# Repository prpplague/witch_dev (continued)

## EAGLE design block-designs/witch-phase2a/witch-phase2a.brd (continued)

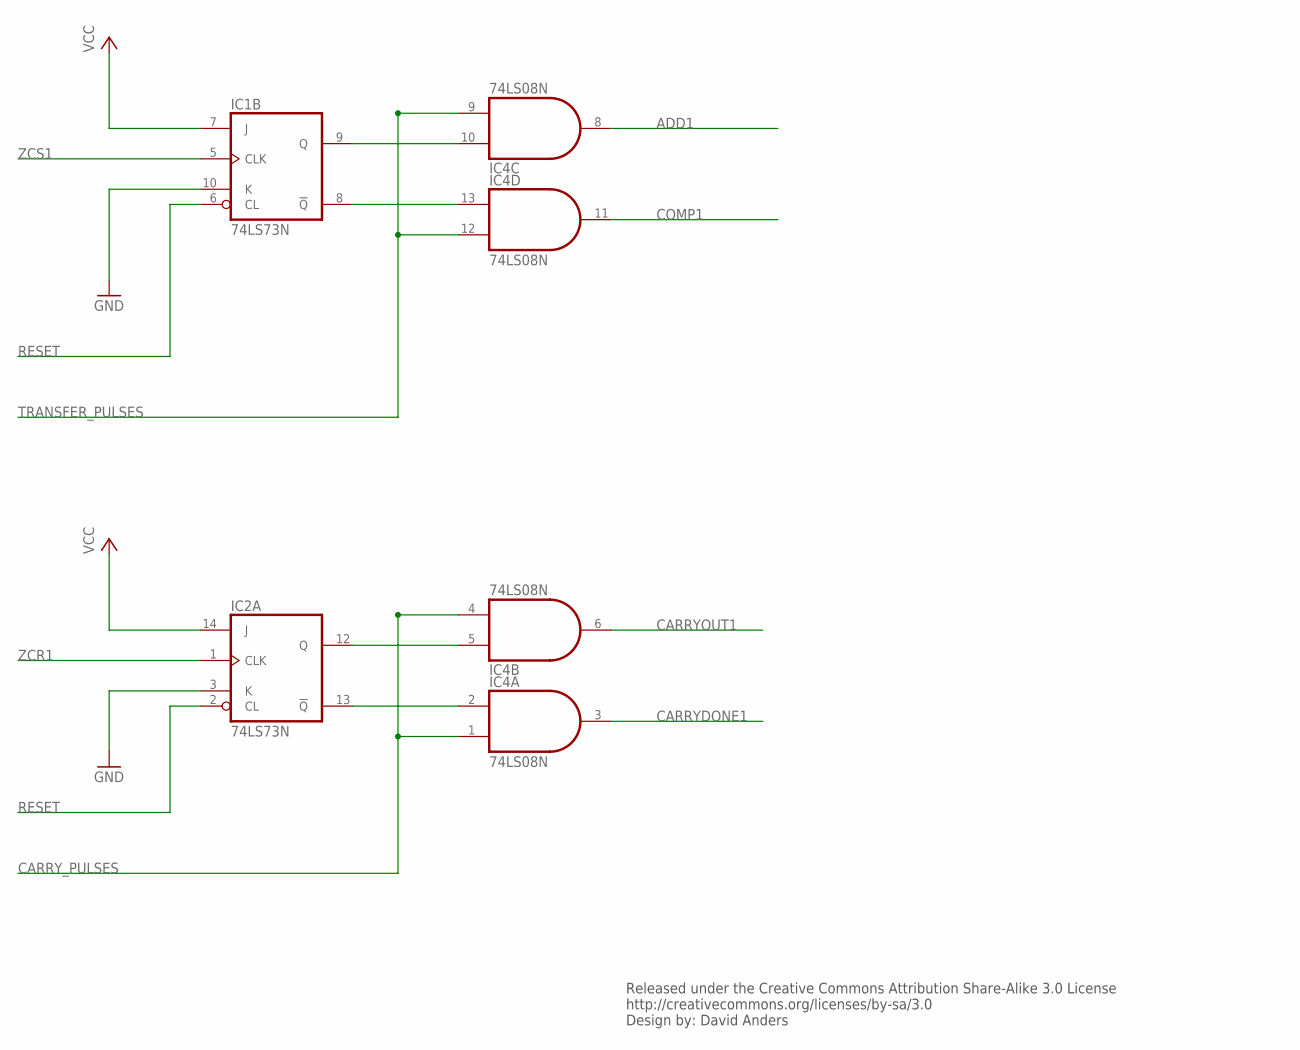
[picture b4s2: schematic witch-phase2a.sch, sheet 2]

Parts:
IC1, IC2: 74LS73N; DIL14
IC4: 74LS08N; DIL14

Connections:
ADD1: IC4.8 (O); also elsewhere on the board
CARRYDONE1: IC4.3 (O); also elsewhere on the board
CARRYOUT1: IC4.6 (O); also elsewhere on the board
CARRY_PULSES: IC4.1 (I0), IC4.4 (I0); also elsewhere on the board
COMP1: IC4.11 (O); also elsewhere on the board
GND: IC1.10 (K), IC2.3 (K); also elsewhere on the board
unnamed: IC2.12 (Q), IC4.5 (I1)
unnamed: IC2.13 (!Q), IC4.2 (I1)
unnamed: IC1.8 (!Q), IC4.13 (I1)
unnamed: IC1.9 (Q), IC4.10 (I1)
RESET: IC1.6 (CL), IC2.2 (CL); also elsewhere on the board
TRANSFER_PULSES: IC4.9 (I0), IC4.12 (I0); also elsewhere on the board
VCC: IC1.7 (J), IC2.14 (J); also elsewhere on the board
ZCR1: IC2.1 (CLK); also elsewhere on the board
ZCS1: IC1.5 (CLK); also elsewhere on the board

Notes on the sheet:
Released under the Creative Commons Attribution Share-Alike 3.0 License http://creativecommons.org/licenses/by-sa/3.0 Design by: David Anders

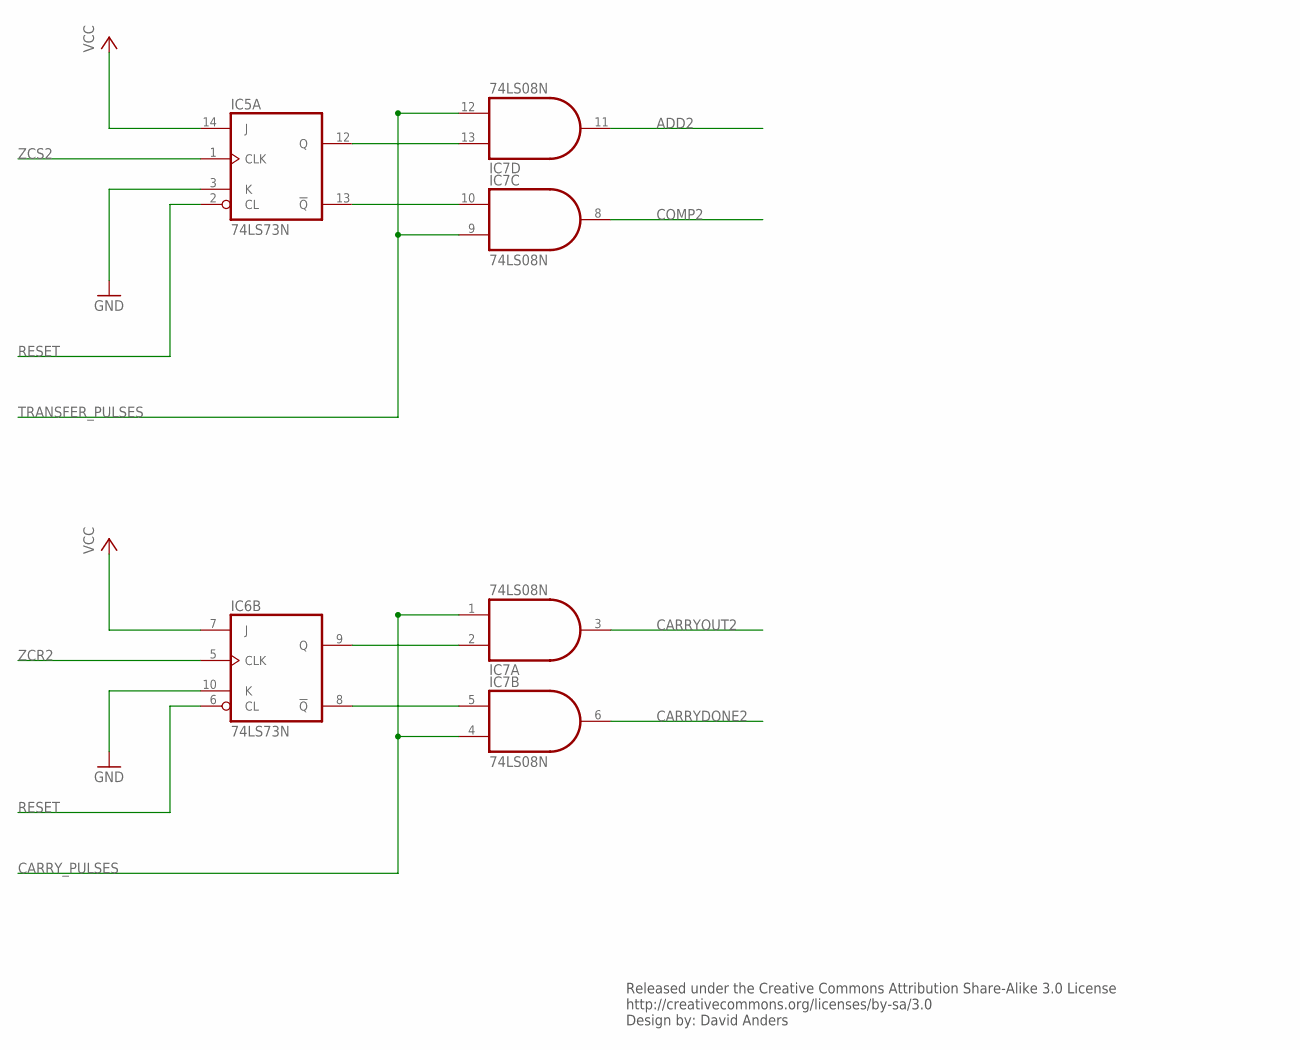
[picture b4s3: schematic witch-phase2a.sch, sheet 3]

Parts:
IC5, IC6: 74LS73N; DIL14
IC7: 74LS08N; DIL14

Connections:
ADD2: IC7.11 (O); also elsewhere on the board
CARRYDONE2: IC7.6 (O); also elsewhere on the board
CARRYOUT2: IC7.3 (O); also elsewhere on the board
CARRY_PULSES: IC7.1 (I0), IC7.4 (I0); also elsewhere on the board
COMP2: IC7.8 (O); also elsewhere on the board
GND: IC5.3 (K), IC6.10 (K); also elsewhere on the board
unnamed: IC6.8 (!Q), IC7.5 (I1)
unnamed: IC5.13 (!Q), IC7.10 (I1)
unnamed: IC5.12 (Q), IC7.13 (I1)
unnamed: IC6.9 (Q), IC7.2 (I1)
RESET: IC5.2 (CL), IC6.6 (CL); also elsewhere on the board
TRANSFER_PULSES: IC7.9 (I0), IC7.12 (I0); also elsewhere on the board
VCC: IC5.14 (J), IC6.7 (J); also elsewhere on the board
ZCR2: IC6.5 (CLK); also elsewhere on the board
ZCS2: IC5.1 (CLK); also elsewhere on the board

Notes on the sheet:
Released under the Creative Commons Attribution Share-Alike 3.0 License http://creativecommons.org/licenses/by-sa/3.0 Design by: David Anders

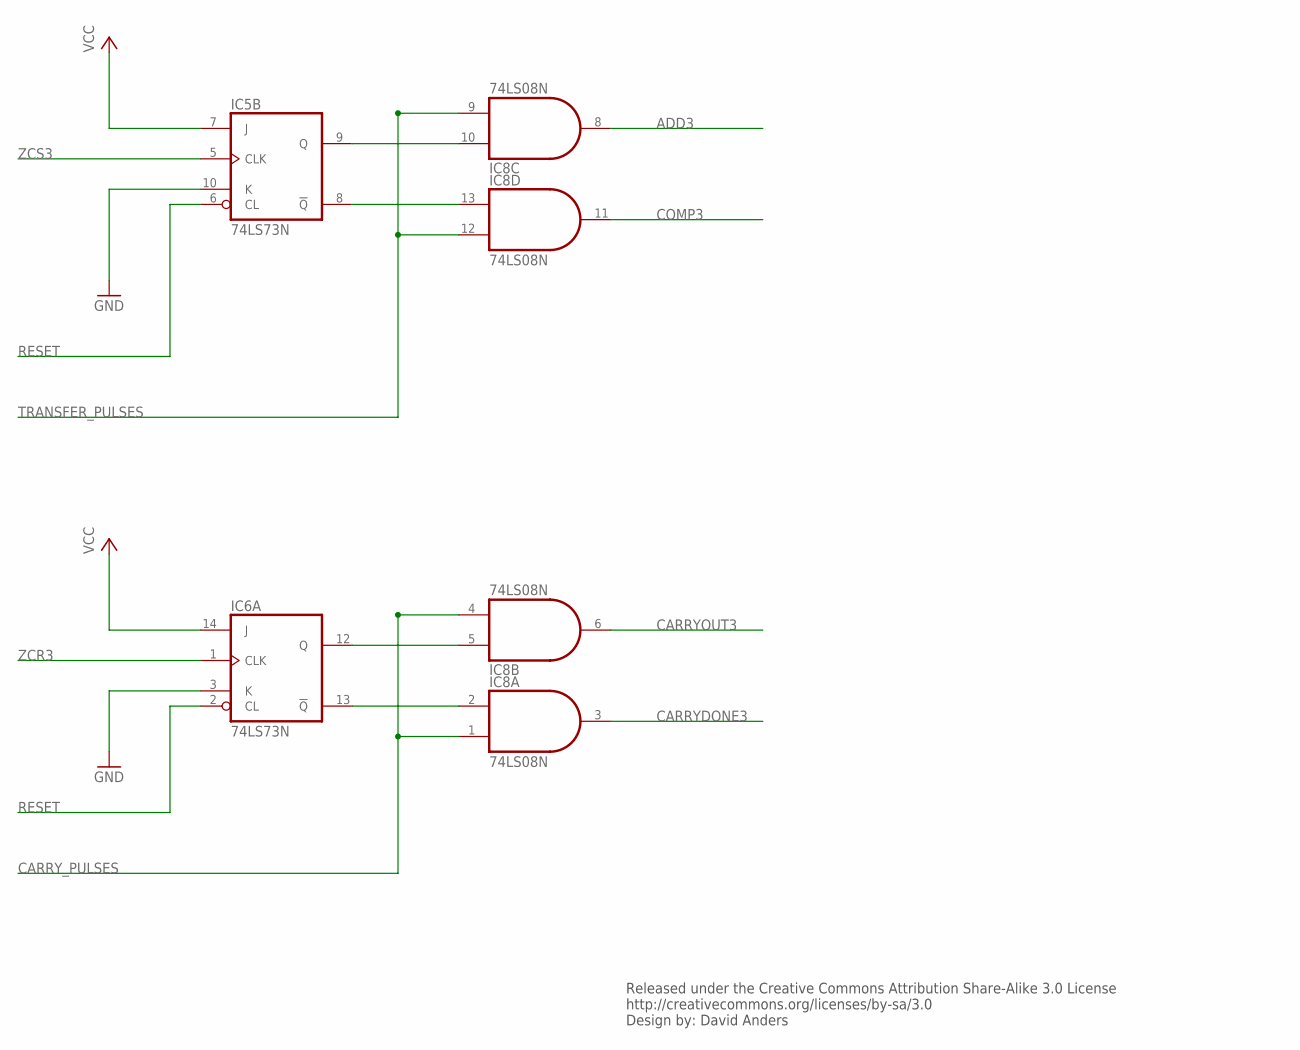
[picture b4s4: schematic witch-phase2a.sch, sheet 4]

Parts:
IC5, IC6: 74LS73N; DIL14
IC8: 74LS08N; DIL14

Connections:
ADD3: IC8.8 (O); also elsewhere on the board
CARRYDONE3: IC8.3 (O); also elsewhere on the board
CARRYOUT3: IC8.6 (O); also elsewhere on the board
CARRY_PULSES: IC8.1 (I0), IC8.4 (I0); also elsewhere on the board
COMP3: IC8.11 (O); also elsewhere on the board
GND: IC5.10 (K), IC6.3 (K); also elsewhere on the board
unnamed: IC6.13 (!Q), IC8.2 (I1)
unnamed: IC5.8 (!Q), IC8.13 (I1)
unnamed: IC5.9 (Q), IC8.10 (I1)
unnamed: IC6.12 (Q), IC8.5 (I1)
RESET: IC5.6 (CL), IC6.2 (CL); also elsewhere on the board
TRANSFER_PULSES: IC8.9 (I0), IC8.12 (I0); also elsewhere on the board
VCC: IC5.7 (J), IC6.14 (J); also elsewhere on the board
ZCR3: IC6.1 (CLK); also elsewhere on the board
ZCS3: IC5.5 (CLK); also elsewhere on the board

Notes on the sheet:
Released under the Creative Commons Attribution Share-Alike 3.0 License http://creativecommons.org/licenses/by-sa/3.0 Design by: David Anders

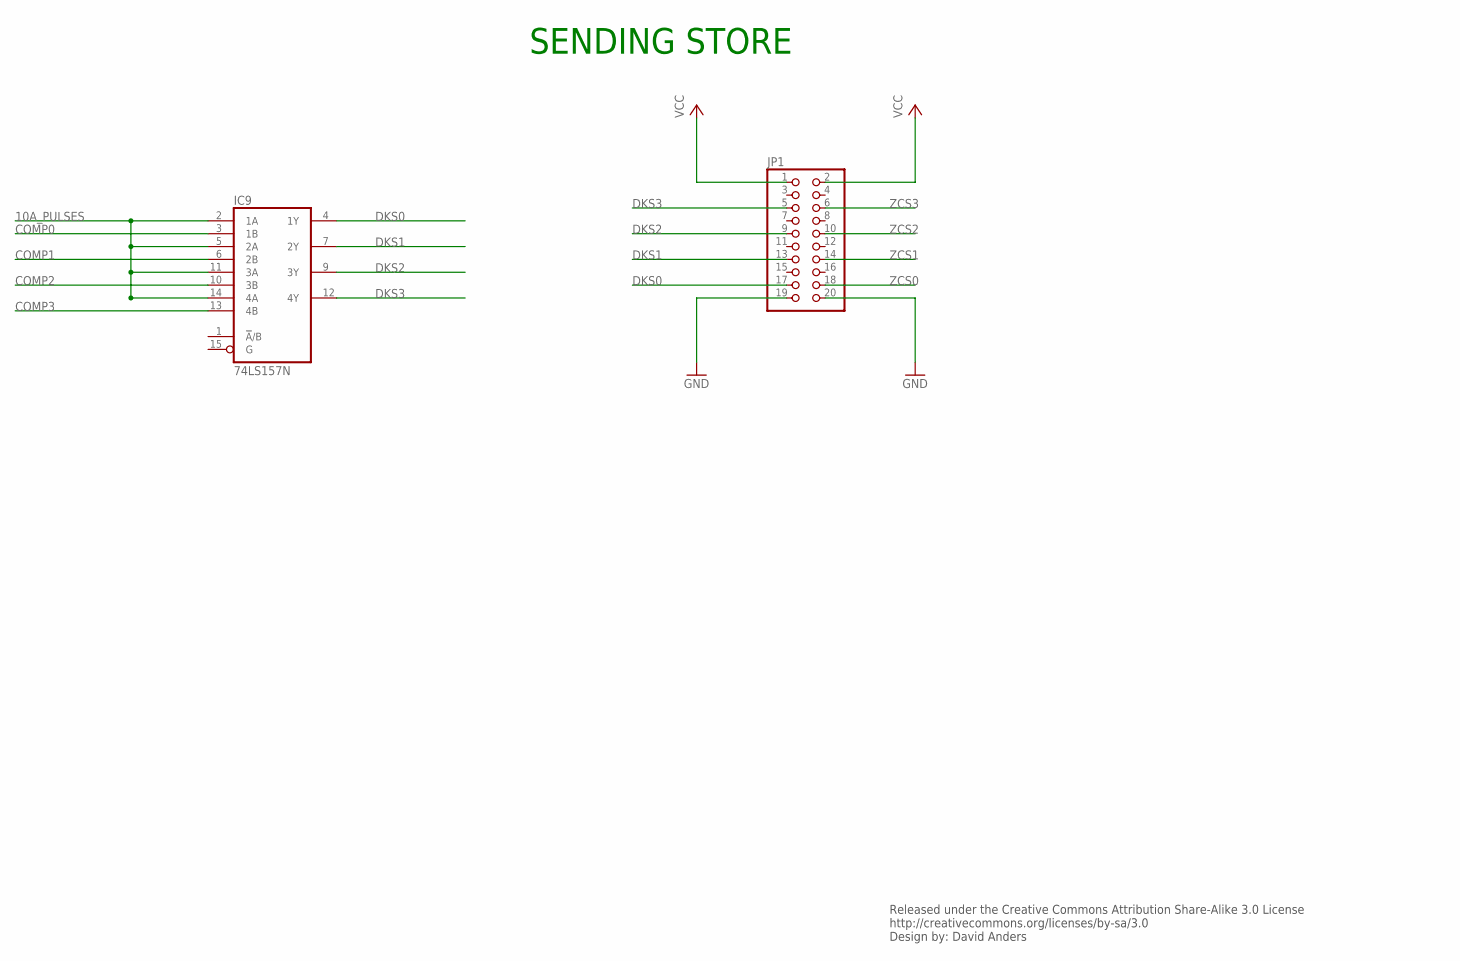
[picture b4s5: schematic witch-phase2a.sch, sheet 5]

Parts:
IC9: 74LS157N; DIL16
JP1: PINHD-2X10; 2X10

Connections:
10A_PULSES: IC9.2 (1A), IC9.5 (2A), IC9.11 (3A), IC9.14 (4A); also elsewhere on the board
COMP0: IC9.3 (1B); also elsewhere on the board
COMP1: IC9.6 (2B); also elsewhere on the board
COMP2: IC9.10 (3B); also elsewhere on the board
COMP3: IC9.13 (4B); also elsewhere on the board
DKS0: IC9.4 (1Y), JP1.17
DKS1: IC9.7 (2Y), JP1.13
DKS2: IC9.9 (3Y), JP1.9
DKS3: IC9.12 (4Y), JP1.5
GND: JP1.19, JP1.20; also elsewhere on the board
VCC: JP1.1, JP1.2; also elsewhere on the board
ZCS0: JP1.18; also elsewhere on the board
ZCS1: JP1.14; also elsewhere on the board
ZCS2: JP1.10; also elsewhere on the board
ZCS3: JP1.6; also elsewhere on the board

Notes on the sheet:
Released under the Creative Commons Attribution Share-Alike 3.0 License http://creativecommons.org/licenses/by-sa/3.0 Design by: David Anders
SENDING STORE

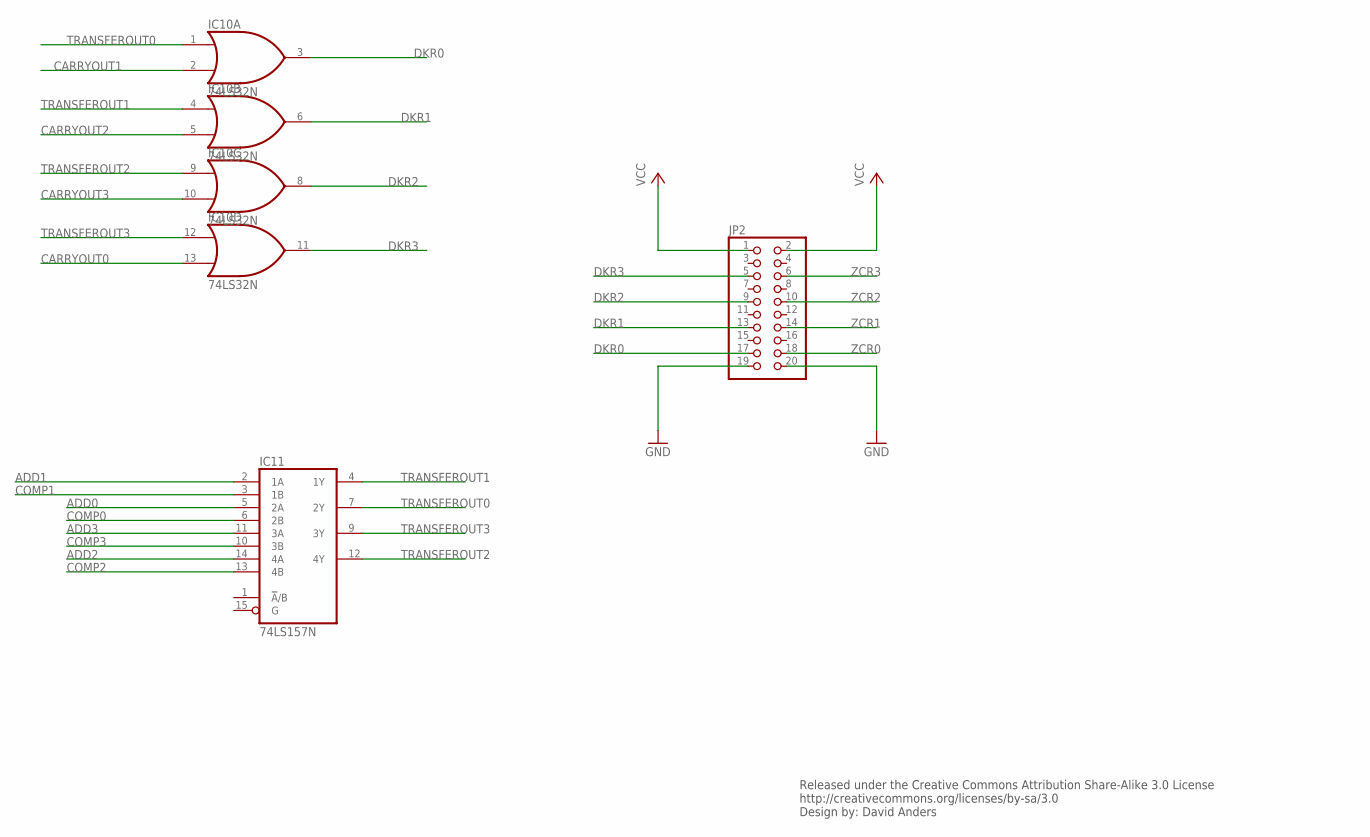
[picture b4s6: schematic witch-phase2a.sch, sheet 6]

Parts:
IC10: 74LS32N; DIL14
IC11: 74LS157N; DIL16
JP2: PINHD-2X10; 2X10

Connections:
ADD0: IC11.5 (2A); also elsewhere on the board
ADD1: IC11.2 (1A); also elsewhere on the board
ADD2: IC11.14 (4A); also elsewhere on the board
ADD3: IC11.11 (3A); also elsewhere on the board
CARRYOUT0: IC10.13 (I1); also elsewhere on the board
CARRYOUT1: IC10.2 (I1); also elsewhere on the board
CARRYOUT2: IC10.5 (I1); also elsewhere on the board
CARRYOUT3: IC10.10 (I1); also elsewhere on the board
COMP0: IC11.6 (2B); also elsewhere on the board
COMP1: IC11.3 (1B); also elsewhere on the board
COMP2: IC11.13 (4B); also elsewhere on the board
COMP3: IC11.10 (3B); also elsewhere on the board
DKR0: IC10.3 (O), JP2.17
DKR1: IC10.6 (O), JP2.13
DKR2: IC10.8 (O), JP2.9
DKR3: IC10.11 (O), JP2.5
GND: JP2.19, JP2.20; also elsewhere on the board
TRANSFEROUT0: IC10.1 (I0), IC11.7 (2Y)
TRANSFEROUT1: IC10.4 (I0), IC11.4 (1Y)
TRANSFEROUT2: IC10.9 (I0), IC11.12 (4Y)
TRANSFEROUT3: IC10.12 (I0), IC11.9 (3Y)
VCC: JP2.1, JP2.2; also elsewhere on the board
ZCR0: JP2.18; also elsewhere on the board
ZCR1: JP2.14; also elsewhere on the board
ZCR2: JP2.10; also elsewhere on the board
ZCR3: JP2.6; also elsewhere on the board

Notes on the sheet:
Released under the Creative Commons Attribution Share-Alike 3.0 License http://creativecommons.org/licenses/by-sa/3.0 Design by: David Anders

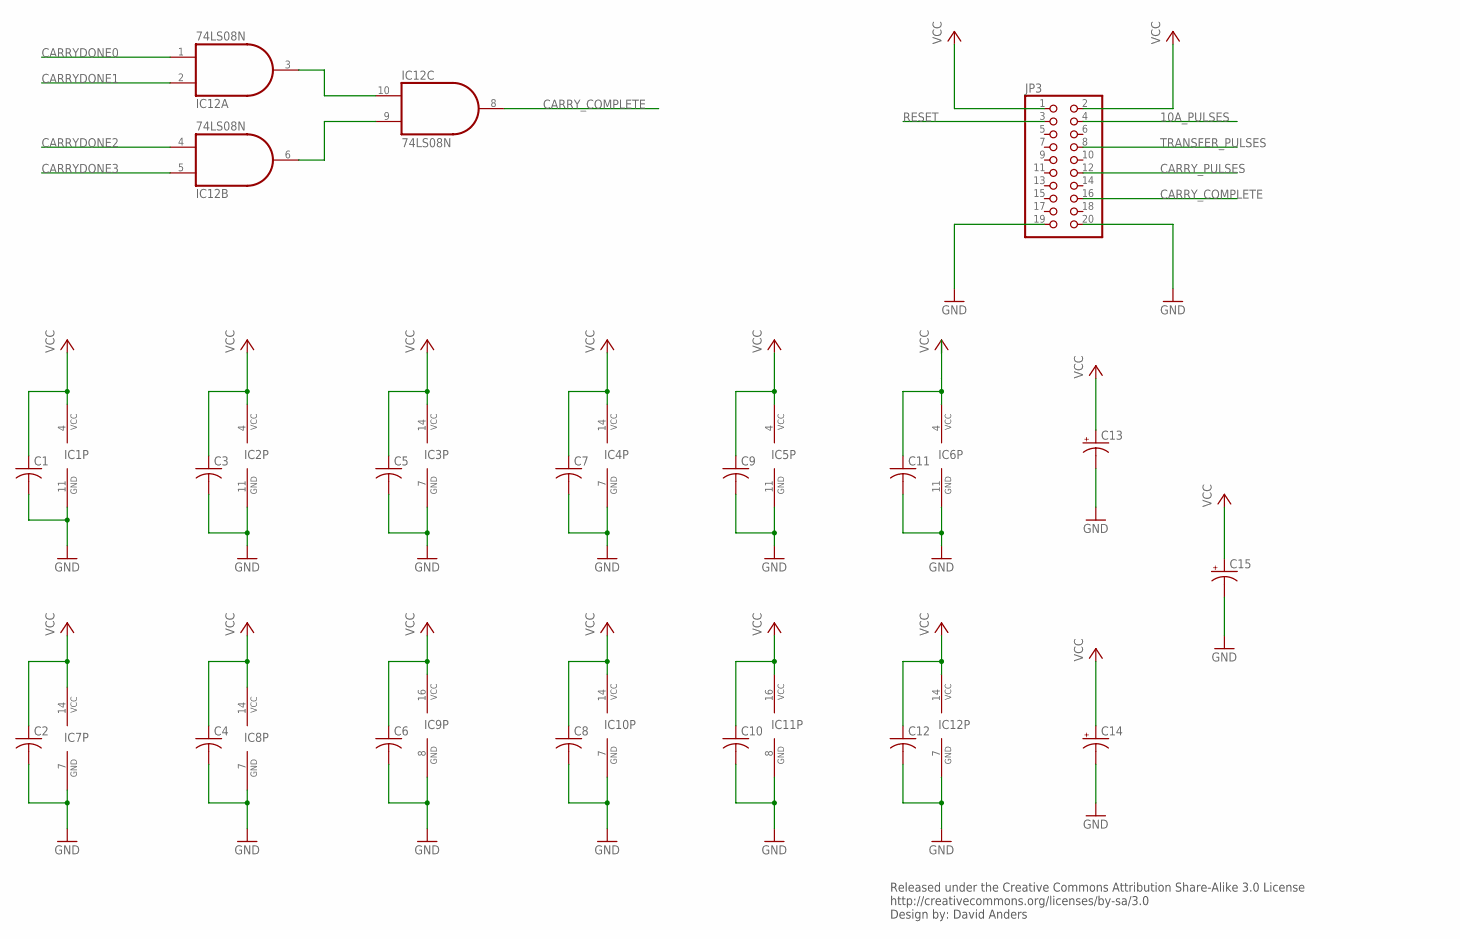
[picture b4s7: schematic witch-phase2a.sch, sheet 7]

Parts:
C1, C2, C3, C4, C5, C6, C7, C8, C9, C10, C11, C12: C-US025-025X050; C025-025X050
C13, C14, C15: CPOL-USE2-5; E2-5
IC1, IC2, IC5, IC6: 74LS73N; DIL14
IC3, IC4, IC7, IC8, IC12: 74LS08N; DIL14
IC9, IC11: 74LS157N; DIL16
IC10: 74LS32N; DIL14
JP3: PINHD-2X10; 2X10

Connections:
10A_PULSES: JP3.4; also elsewhere on the board
CARRYDONE0: IC12.1 (I0); also elsewhere on the board
CARRYDONE1: IC12.2 (I1); also elsewhere on the board
CARRYDONE2: IC12.4 (I0); also elsewhere on the board
CARRYDONE3: IC12.5 (I1); also elsewhere on the board
CARRY_COMPLETE: IC12.8 (O), JP3.16
CARRY_PULSES: JP3.12; also elsewhere on the board
GND: C1.2, C2.2, C3.2, C4.2, C5.2, C6.2, C7.2, C8.2, C9.2, C10.2, C11.2, C12.2, C13.-, C14.-, C15.-, IC1.11 (GND), IC2.11 (GND), IC3.7 (GND), IC4.7 (GND), IC5.11 (GND), IC6.11 (GND), IC7.7 (GND), IC8.7 (GND), IC9.8 (GND), IC10.7 (GND), IC11.8 (GND), IC12.7 (GND), JP3.19, JP3.20; also elsewhere on the board
unnamed: IC12.3 (O), IC12.10 (I1)
unnamed: IC12.6 (O), IC12.9 (I0)
RESET: JP3.3; also elsewhere on the board
TRANSFER_PULSES: JP3.8; also elsewhere on the board
VCC: C1.1, C2.1, C3.1, C4.1, C5.1, C6.1, C7.1, C8.1, C9.1, C10.1, C11.1, C12.1, C13.+, C14.+, C15.+, IC1.4 (VCC), IC2.4 (VCC), IC3.14 (VCC), IC4.14 (VCC), IC5.4 (VCC), IC6.4 (VCC), IC7.14 (VCC), IC8.14 (VCC), IC9.16 (VCC), IC10.14 (VCC), IC11.16 (VCC), IC12.14 (VCC), JP3.1, JP3.2; also elsewhere on the board

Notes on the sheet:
Released under the Creative Commons Attribution Share-Alike 3.0 License http://creativecommons.org/licenses/by-sa/3.0 Design by: David Anders

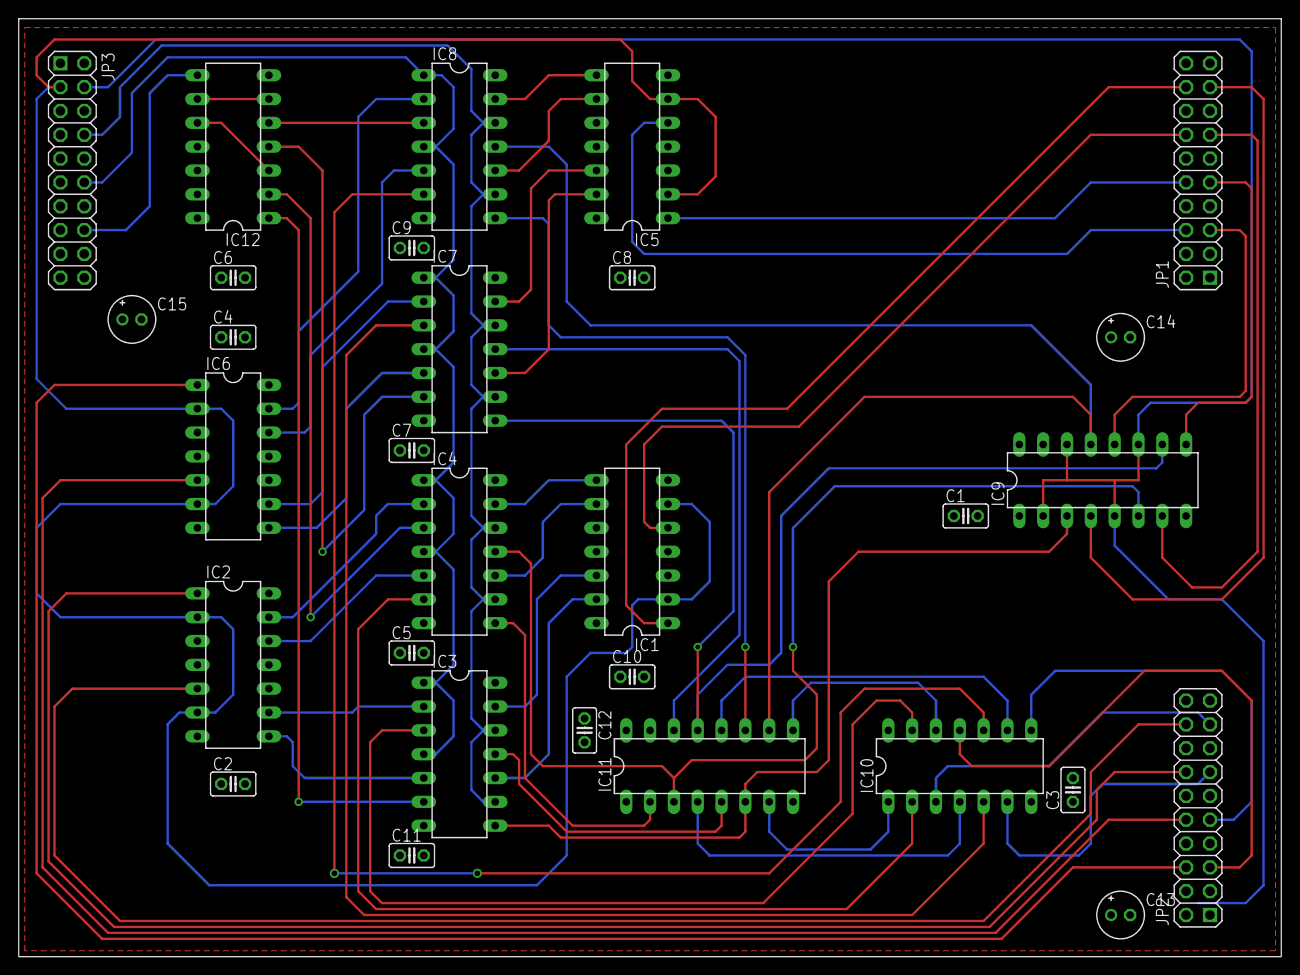
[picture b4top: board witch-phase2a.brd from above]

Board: 2 copper layers, 134.6 x 100.0 mm, 30 parts (0 on the bottom side), 61 nets.

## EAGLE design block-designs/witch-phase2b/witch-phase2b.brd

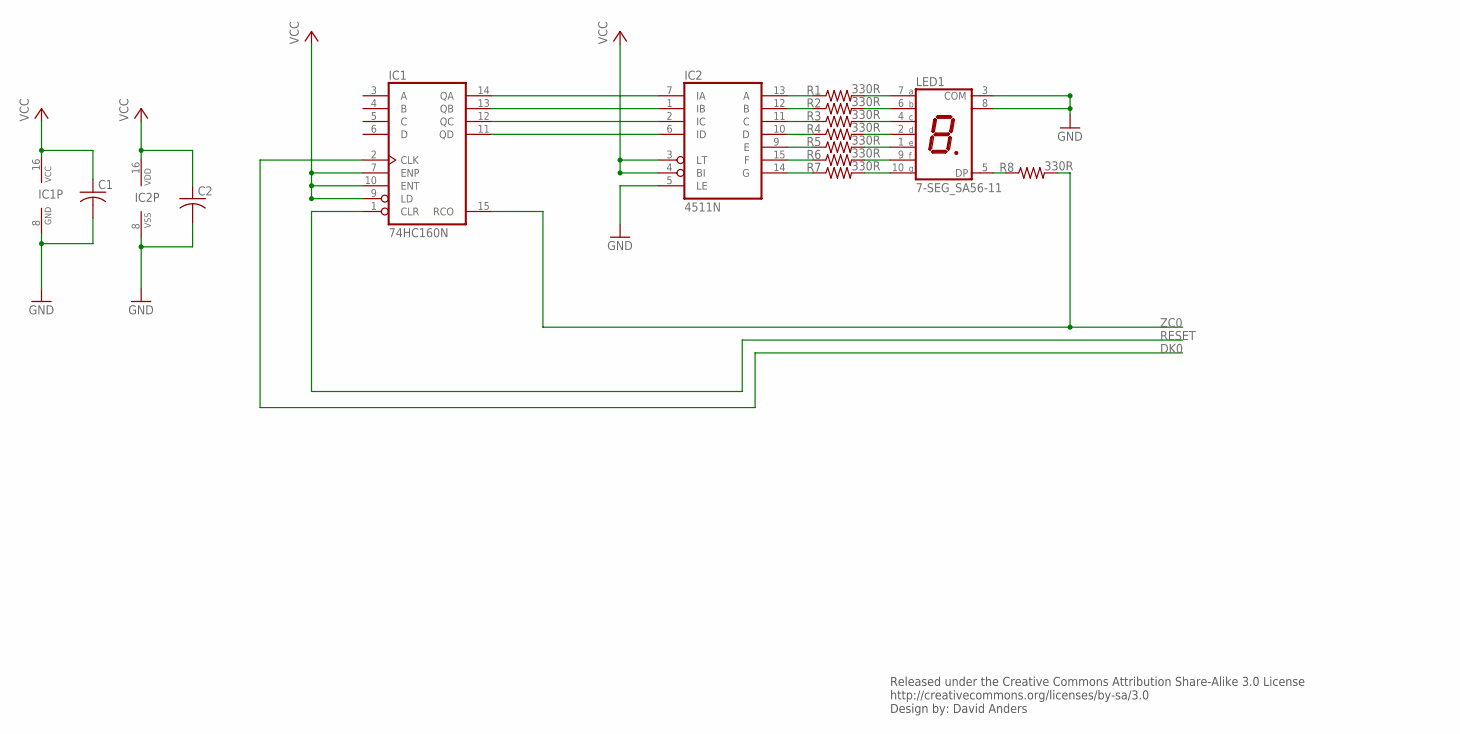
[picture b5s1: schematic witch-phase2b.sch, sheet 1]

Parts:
C1, C2: C-US025-025X050; C025-025X050
IC1: 74HC160N; DIL16
IC2: 4511N; DIL16
LED1: 7-SEG_SA56-11; SA56-11
R1, R2, R3, R4, R5, R6, R7, R8: 330R; 0204/5

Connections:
DK0: IC1.2 (CLK); also elsewhere on the board
GND: C1.2, C2.2, IC1.8 (GND), IC2.5 (LE), IC2.8 (VSS), LED1.3 (COM), LED1.8 (COM); also elsewhere on the board
unnamed: IC2.13 (A), R1.1
unnamed: IC2.12 (B), R2.1
unnamed: IC2.11 (C), R3.1
unnamed: IC2.10 (D), R4.1
unnamed: IC2.9 (E), R5.1
unnamed: IC2.15 (F), R6.1
unnamed: IC2.14 (G), R7.1
unnamed: IC1.14 (QA), IC2.7 (IA)
unnamed: IC1.13 (QB), IC2.1 (IB)
unnamed: IC1.12 (QC), IC2.2 (IC)
unnamed: IC1.11 (QD), IC2.6 (ID)
unnamed: LED1.7 (A), R1.2
unnamed: LED1.6 (B), R2.2
unnamed: LED1.4 (C), R3.2
unnamed: LED1.2 (D), R4.2
unnamed: LED1.1 (E), R5.2
unnamed: LED1.9 (F), R6.2
unnamed: LED1.10 (G), R7.2
unnamed: LED1.5 (DP), R8.1
RESET: IC1.1 (CLR); also elsewhere on the board
VCC: C1.1, C2.1, IC1.7 (ENP), IC1.9 (LD), IC1.10 (ENT), IC1.16 (VCC), IC2.3 (LT), IC2.4 (BI), IC2.16 (VDD); also elsewhere on the board
ZC0: IC1.15 (RCO), R8.2; also elsewhere on the board

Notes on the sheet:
Released under the Creative Commons Attribution Share-Alike 3.0 License http://creativecommons.org/licenses/by-sa/3.0 Design by: David Anders

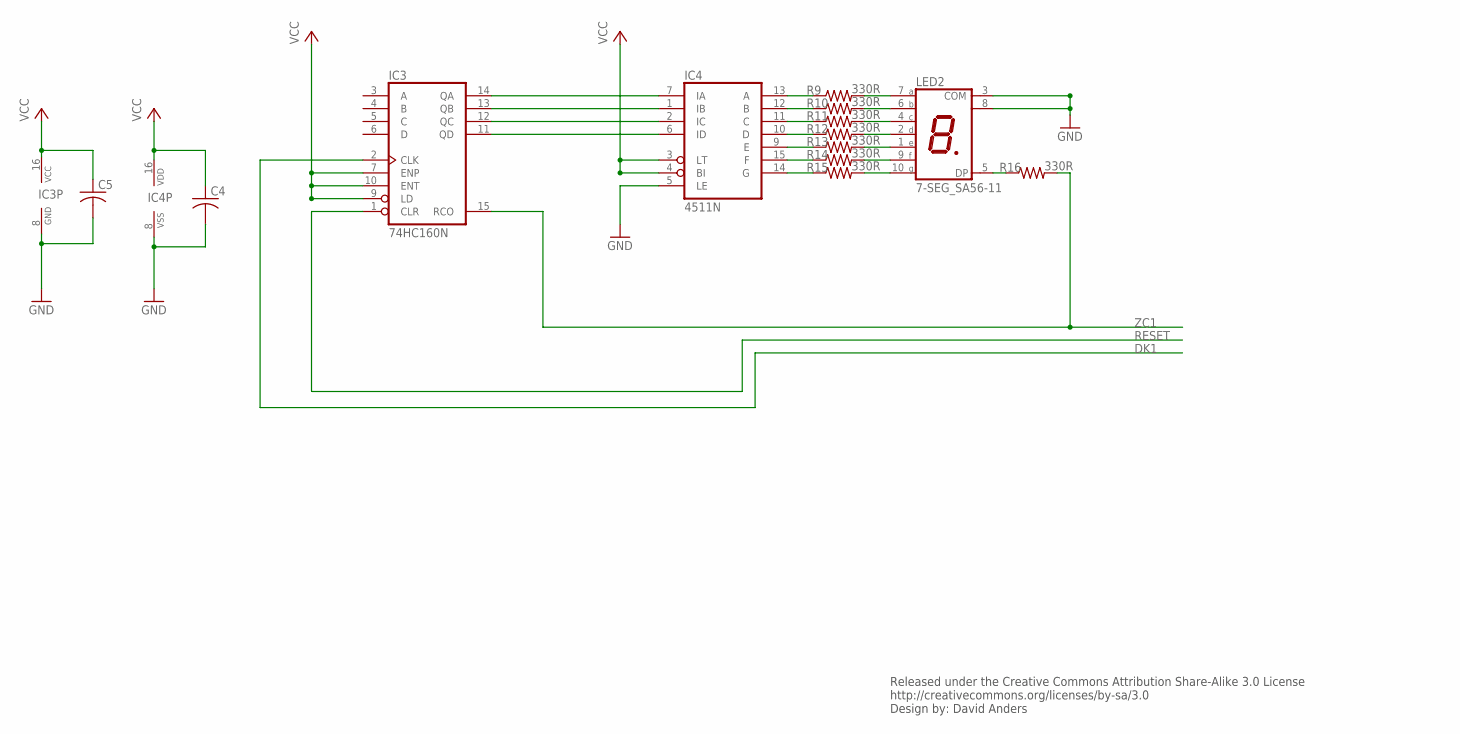
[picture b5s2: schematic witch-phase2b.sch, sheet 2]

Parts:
C4, C5: C-US025-025X050; C025-025X050
IC3: 74HC160N; DIL16
IC4: 4511N; DIL16
LED2: 7-SEG_SA56-11; SA56-11
R9, R10, R11, R12, R13, R14, R15, R16: 330R; 0204/5

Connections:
DK1: IC3.2 (CLK); also elsewhere on the board
GND: C4.2, C5.2, IC3.8 (GND), IC4.5 (LE), IC4.8 (VSS), LED2.3 (COM), LED2.8 (COM); also elsewhere on the board
unnamed: IC3.14 (QA), IC4.7 (IA)
unnamed: IC3.13 (QB), IC4.1 (IB)
unnamed: IC3.12 (QC), IC4.2 (IC)
unnamed: IC3.11 (QD), IC4.6 (ID)
unnamed: IC4.13 (A), R9.1
unnamed: IC4.12 (B), R10.1
unnamed: IC4.11 (C), R11.1
unnamed: IC4.10 (D), R12.1
unnamed: IC4.9 (E), R13.1
unnamed: IC4.15 (F), R14.1
unnamed: IC4.14 (G), R15.1
unnamed: LED2.7 (A), R9.2
unnamed: LED2.6 (B), R10.2
unnamed: LED2.4 (C), R11.2
unnamed: LED2.2 (D), R12.2
unnamed: LED2.1 (E), R13.2
unnamed: LED2.9 (F), R14.2
unnamed: LED2.10 (G), R15.2
unnamed: LED2.5 (DP), R16.1
RESET: IC3.1 (CLR); also elsewhere on the board
VCC: C4.1, C5.1, IC3.7 (ENP), IC3.9 (LD), IC3.10 (ENT), IC3.16 (VCC), IC4.3 (LT), IC4.4 (BI), IC4.16 (VDD); also elsewhere on the board
ZC1: IC3.15 (RCO), R16.2; also elsewhere on the board

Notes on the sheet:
Released under the Creative Commons Attribution Share-Alike 3.0 License http://creativecommons.org/licenses/by-sa/3.0 Design by: David Anders

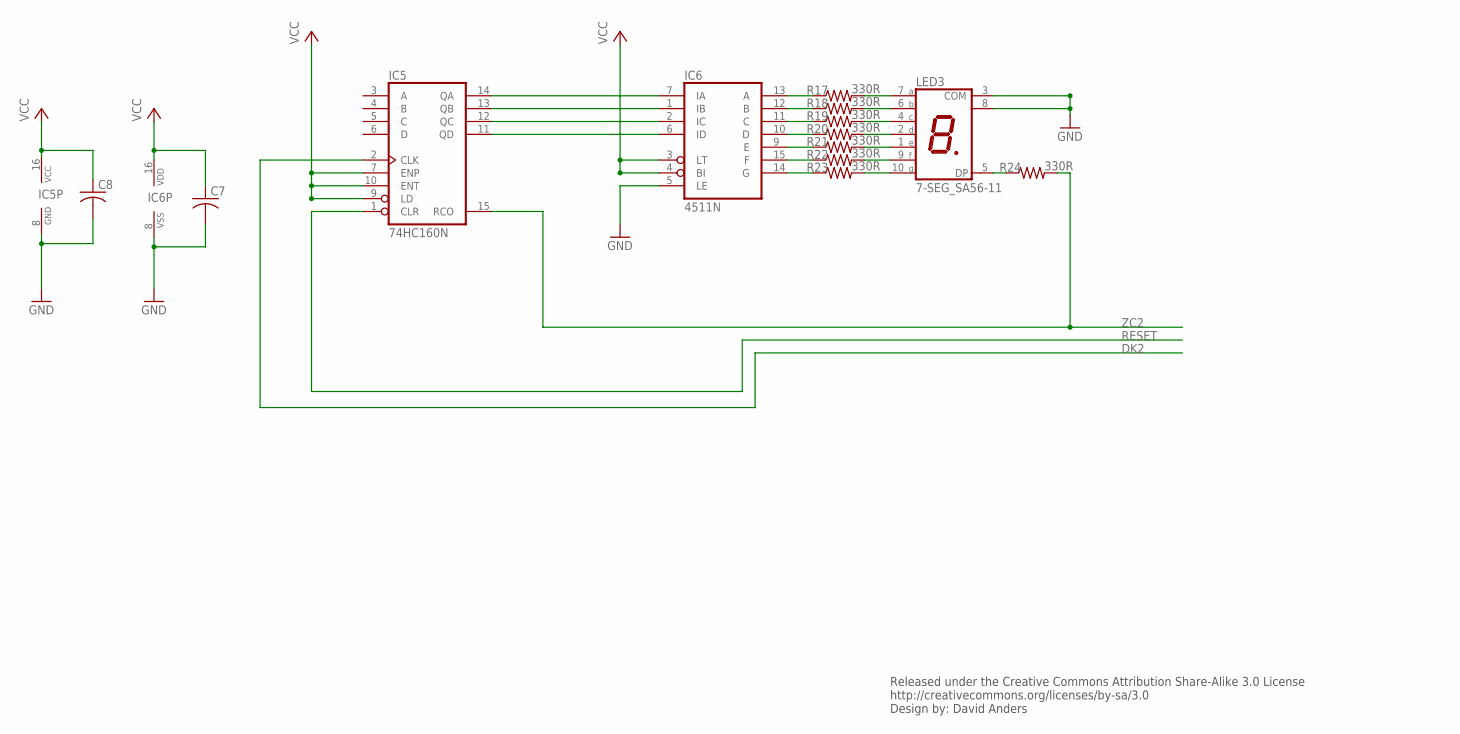
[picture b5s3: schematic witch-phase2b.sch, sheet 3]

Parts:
C7, C8: C-US025-025X050; C025-025X050
IC5: 74HC160N; DIL16
IC6: 4511N; DIL16
LED3: 7-SEG_SA56-11; SA56-11
R17, R18, R19, R20, R21, R22, R23, R24: 330R; 0204/5

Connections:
DK2: IC5.2 (CLK); also elsewhere on the board
GND: C7.2, C8.2, IC5.8 (GND), IC6.5 (LE), IC6.8 (VSS), LED3.3 (COM), LED3.8 (COM); also elsewhere on the board
unnamed: IC5.14 (QA), IC6.7 (IA)
unnamed: IC5.13 (QB), IC6.1 (IB)
unnamed: IC5.12 (QC), IC6.2 (IC)
unnamed: IC5.11 (QD), IC6.6 (ID)
unnamed: IC6.13 (A), R17.1
unnamed: IC6.12 (B), R18.1
unnamed: IC6.11 (C), R19.1
unnamed: IC6.10 (D), R20.1
unnamed: IC6.9 (E), R21.1
unnamed: IC6.15 (F), R22.1
unnamed: IC6.14 (G), R23.1
unnamed: LED3.7 (A), R17.2
unnamed: LED3.6 (B), R18.2
unnamed: LED3.4 (C), R19.2
unnamed: LED3.2 (D), R20.2
unnamed: LED3.1 (E), R21.2
unnamed: LED3.9 (F), R22.2
unnamed: LED3.10 (G), R23.2
unnamed: LED3.5 (DP), R24.1
RESET: IC5.1 (CLR); also elsewhere on the board
VCC: C7.1, C8.1, IC5.7 (ENP), IC5.9 (LD), IC5.10 (ENT), IC5.16 (VCC), IC6.3 (LT), IC6.4 (BI), IC6.16 (VDD); also elsewhere on the board
ZC2: IC5.15 (RCO), R24.2; also elsewhere on the board

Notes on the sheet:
Released under the Creative Commons Attribution Share-Alike 3.0 License http://creativecommons.org/licenses/by-sa/3.0 Design by: David Anders

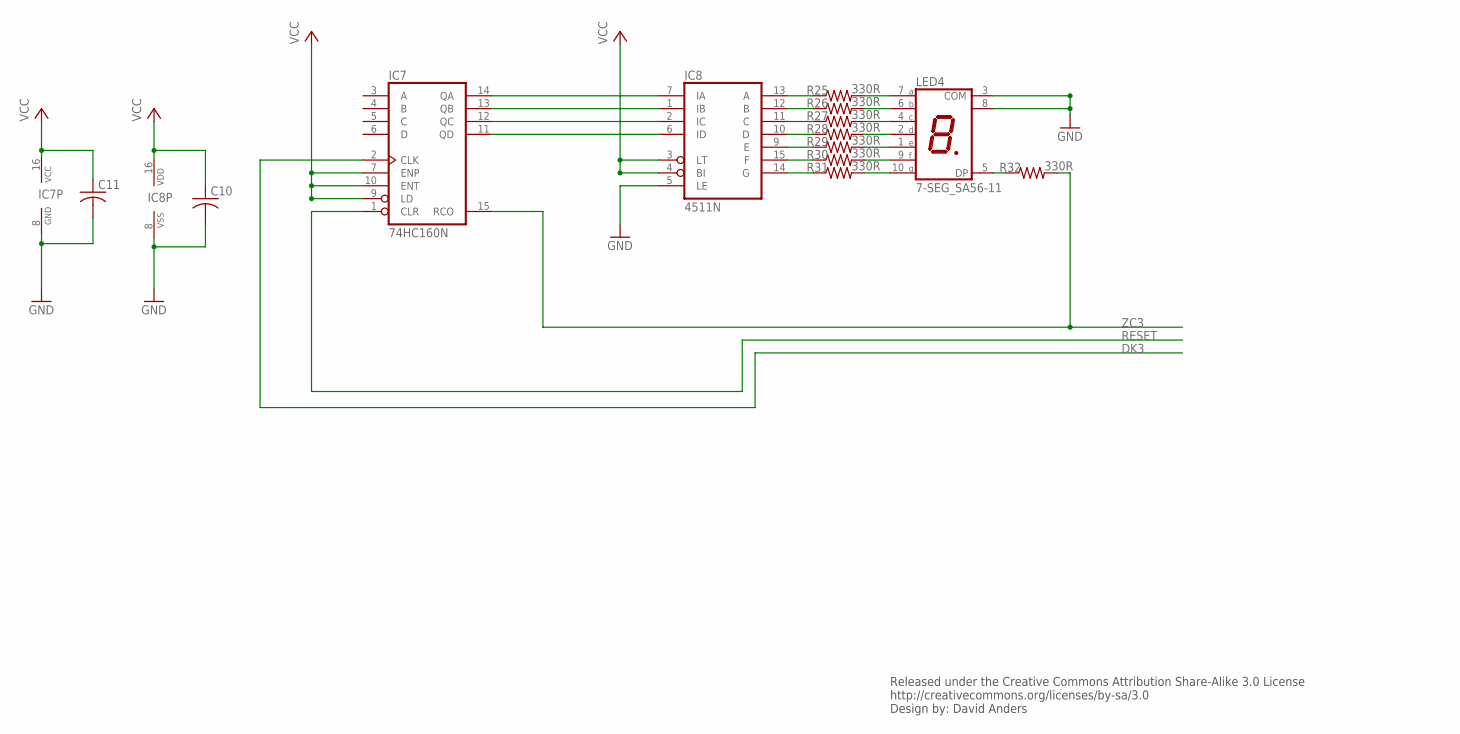
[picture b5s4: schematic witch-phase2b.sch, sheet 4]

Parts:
C10, C11: C-US025-025X050; C025-025X050
IC7: 74HC160N; DIL16
IC8: 4511N; DIL16
LED4: 7-SEG_SA56-11; SA56-11
R25, R26, R27, R28, R29, R30, R31, R32: 330R; 0204/5

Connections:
DK3: IC7.2 (CLK); also elsewhere on the board
GND: C10.2, C11.2, IC7.8 (GND), IC8.5 (LE), IC8.8 (VSS), LED4.3 (COM), LED4.8 (COM); also elsewhere on the board
unnamed: IC7.14 (QA), IC8.7 (IA)
unnamed: IC7.13 (QB), IC8.1 (IB)
unnamed: IC7.12 (QC), IC8.2 (IC)
unnamed: IC7.11 (QD), IC8.6 (ID)
unnamed: IC8.13 (A), R25.1
unnamed: IC8.12 (B), R26.1
unnamed: IC8.11 (C), R27.1
unnamed: IC8.10 (D), R28.1
unnamed: IC8.9 (E), R29.1
unnamed: IC8.15 (F), R30.1
unnamed: IC8.14 (G), R31.1
unnamed: LED4.7 (A), R25.2
unnamed: LED4.6 (B), R26.2
unnamed: LED4.4 (C), R27.2
unnamed: LED4.2 (D), R28.2
unnamed: LED4.1 (E), R29.2
unnamed: LED4.9 (F), R30.2
unnamed: LED4.10 (G), R31.2
unnamed: LED4.5 (DP), R32.1
RESET: IC7.1 (CLR); also elsewhere on the board
VCC: C10.1, C11.1, IC7.7 (ENP), IC7.9 (LD), IC7.10 (ENT), IC7.16 (VCC), IC8.3 (LT), IC8.4 (BI), IC8.16 (VDD); also elsewhere on the board
ZC3: IC7.15 (RCO), R32.2; also elsewhere on the board

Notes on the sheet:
Released under the Creative Commons Attribution Share-Alike 3.0 License http://creativecommons.org/licenses/by-sa/3.0 Design by: David Anders
